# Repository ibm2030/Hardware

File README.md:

# Hardware
Boards for LEDs and switches etc.
Note that the x_PCB pdf is provided for reference only as it excludes the ground and power planes so appears incomplete.

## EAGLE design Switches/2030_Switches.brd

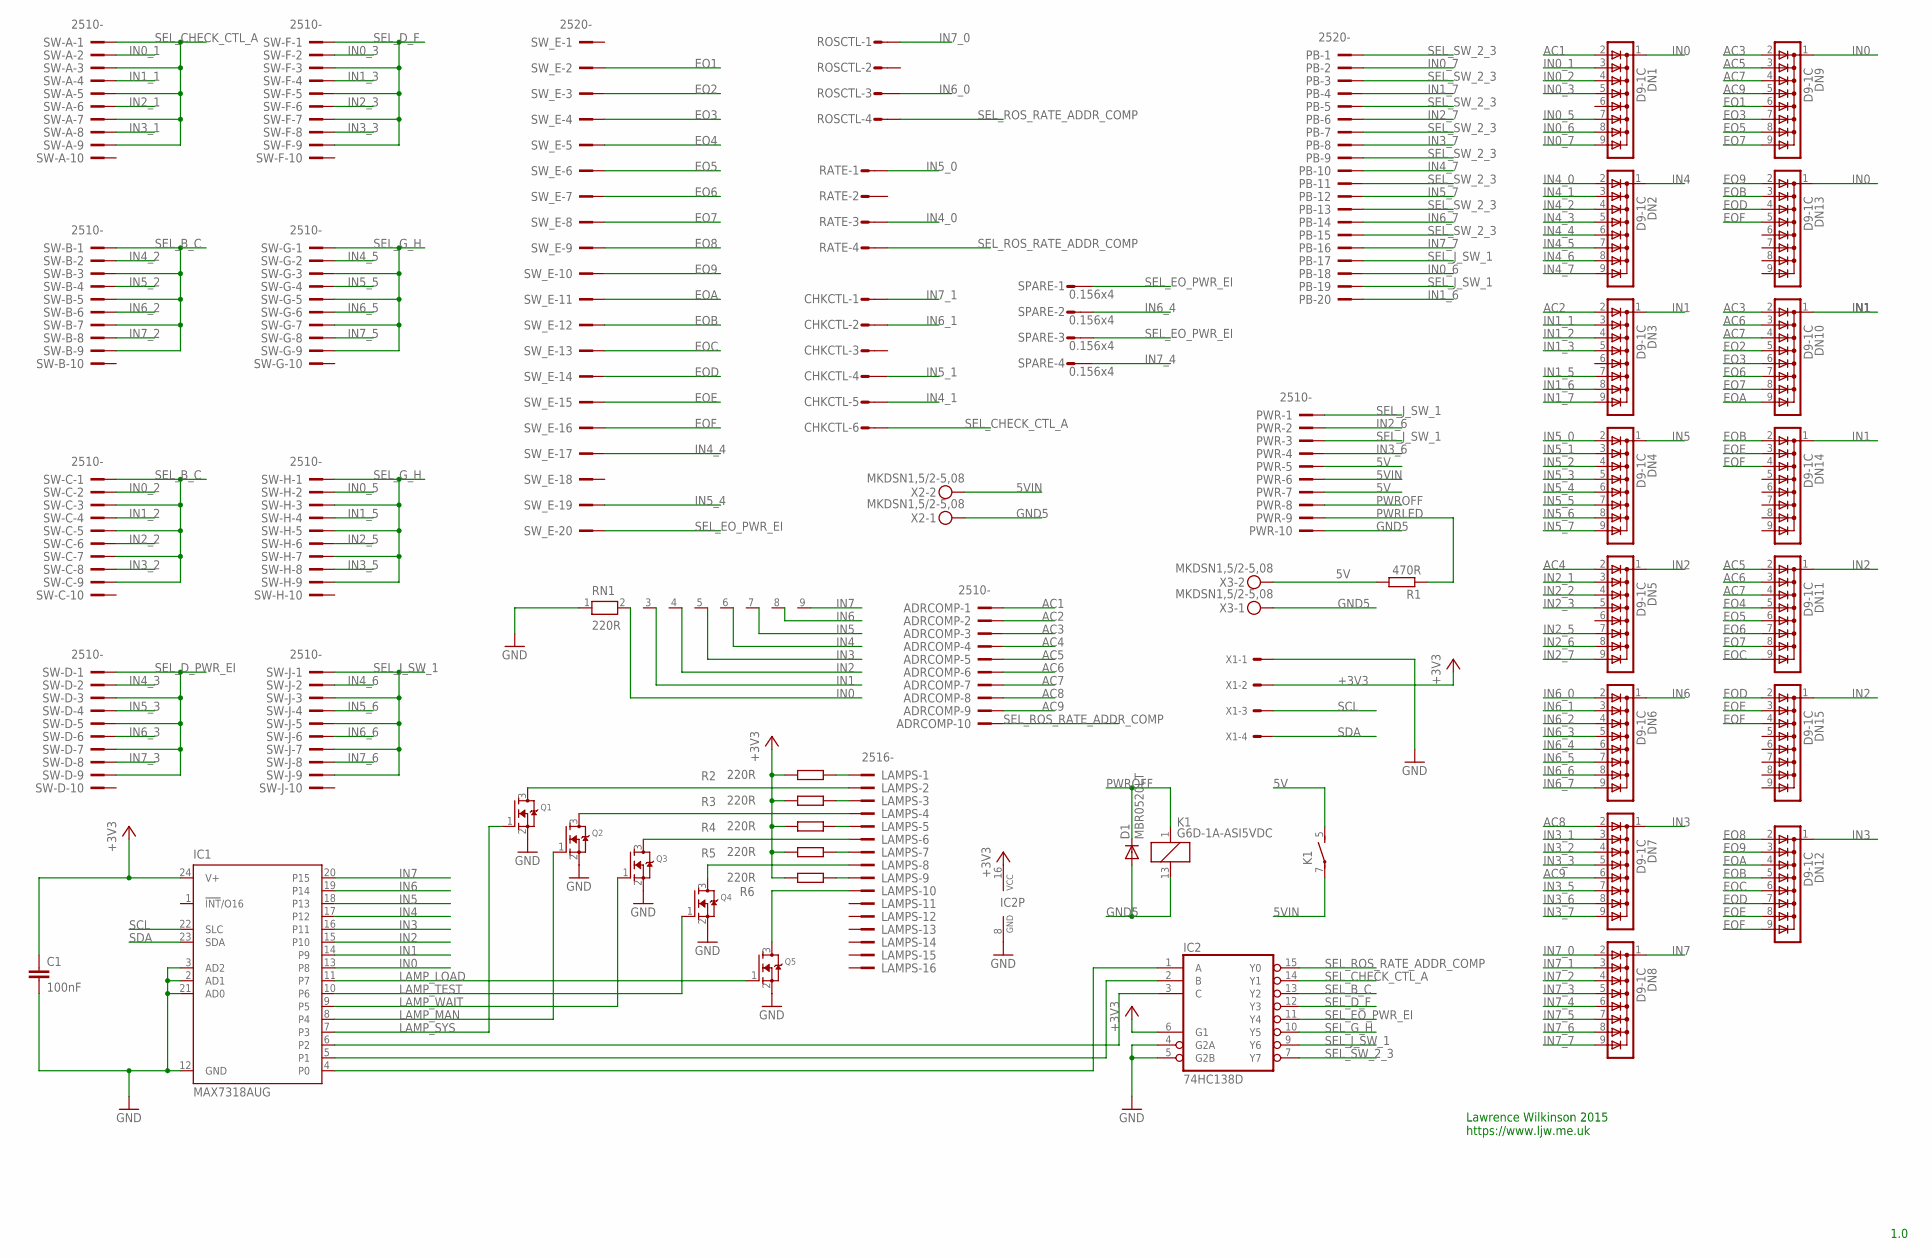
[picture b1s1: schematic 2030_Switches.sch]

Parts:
ADRCOMP: 2510-; PAK100/2500-10
C1: 100nF; C1206
CHKCTL: S06P
D1: MBR0520LT; SOD123
DN1, DN2, DN3, DN4, DN5, DN6, DN7, DN8, DN9, DN10, DN11, DN12, DN13, DN14, DN15: D9-1C; SIL09C
IC1: MAX7318AUG; SO24L
IC2: 74HC138D; SO16
K1: G6D-1A-ASI5VDC; G6D
LAMPS: 2516-; PAK100/2500-16
PB: 2520-; PAK100/2500-20
PWR: 2510-; PAK100/2500-10
Q1, Q2, Q3, Q4, Q5: MOSFET-NREFLOW; SOT23
R1: 470R; M1206
R2, R3, R4, R5, R6: 220R; R0805
RATE: S04P
RN1: 220R; RN-9
ROSCTL: S04P
SPARE: 0.156x4; S04P
SW-A: 2510-; PAK100/2500-10
SW-B: 2510-; PAK100/2500-10
SW-C: 2510-; PAK100/2500-10
SW-D: 2510-; PAK100/2500-10
SW-F: 2510-; PAK100/2500-10
SW-G: 2510-; PAK100/2500-10
SW-H: 2510-; PAK100/2500-10
SW-J: 2510-; PAK100/2500-10
SW_E: 2520-; PAK100/2500-20
X1: KK-156-4
X2, X3: MKDSN1,5/2-5,08

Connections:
5V: K1.5 (S), PWR.5, PWR.7, R1.2, X3.2
5VIN: K1.7, PWR.6, X2.2
+3V3: C1.1, IC1.24 (V+), IC2.6 (G1), IC2.16 (VCC), R2.1, R3.1, R4.1, R5.1, R6.1, X1.2
AC1: ADRCOMP.1, DN1.2
AC2: ADRCOMP.2, DN3.2
AC3: ADRCOMP.3, DN9.2, DN10.2
AC4: ADRCOMP.4, DN5.2
AC5: ADRCOMP.5, DN9.3, DN11.2
AC6: ADRCOMP.6, DN10.3, DN11.3
AC7: ADRCOMP.7, DN9.4, DN10.4, DN11.4
AC8: ADRCOMP.8, DN7.2
AC9: ADRCOMP.9, DN7.6, DN9.5
EO1: DN9.6, SW_E.2
EO2: DN10.5, SW_E.3
EO3: DN9.7, DN10.6, SW_E.4
EO4: DN11.5, SW_E.5
EO5: DN9.8, DN11.6, SW_E.6
EO6: DN10.7, DN11.7, SW_E.7
EO7: DN9.9, DN10.8, DN11.8, SW_E.8
EO8: DN12.2, SW_E.9
EO9: DN12.3, DN13.2, SW_E.10
EOA: DN10.9, DN12.4, SW_E.11
EOB: DN12.5, DN13.3, DN14.2, SW_E.12
EOC: DN11.9, DN12.6, SW_E.13
EOD: DN12.7, DN13.4, DN15.2, SW_E.14
EOE: DN12.8, DN14.3, DN15.3, SW_E.15
EOF: DN12.9, DN13.5, DN14.4, DN15.4, SW_E.16
GND: C1.2, IC1.2 (AD1), IC1.3 (AD2), IC1.12 (GND), IC1.21 (AD0), IC2.4 (G2A), IC2.5 (G2B), IC2.8 (GND), Q1.2 (S), Q2.2 (S), Q3.2 (S), Q4.2 (S), Q5.2 (S), RN1.1, X1.1
GND5: D1.A, K1.13 (2), PWR.10, X2.1, X3.1
IN0: DN1.1 (C), DN9.1 (C), DN13.1 (C), IC1.13 (P8), RN1.2
IN0_1: DN1.3, SW-A.2
IN0_2: DN1.4, SW-C.2
IN0_3: DN1.5, SW-F.2
IN0_5: DN1.7, SW-H.2
IN0_6: DN1.8, PB.18
IN0_7: DN1.9, PB.2
IN1: DN3.1 (C), DN10.1 (C), DN14.1 (C), IC1.14 (P9), RN1.3
IN1_1: DN3.3, SW-A.4
IN1_2: DN3.4, SW-C.4
IN1_3: DN3.5, SW-F.4
IN1_5: DN3.7, SW-H.4
IN1_6: DN3.8, PB.20
IN1_7: DN3.9, PB.4
IN2: DN5.1 (C), DN11.1 (C), DN15.1 (C), IC1.15 (P10), RN1.4
IN2_1: DN5.3, SW-A.6
IN2_2: DN5.4, SW-C.6
IN2_3: DN5.5, SW-F.6
IN2_5: DN5.7, SW-H.6
IN2_6: DN5.8, PWR.2
IN2_7: DN5.9, PB.6
IN3: DN7.1 (C), DN12.1 (C), IC1.16 (P11), RN1.5
IN3_1: DN7.3, SW-A.8
IN3_2: DN7.4, SW-C.8
IN3_3: DN7.5, SW-F.8
IN3_5: DN7.7, SW-H.8
IN3_6: DN7.8, PWR.4
IN3_7: DN7.9, PB.8
IN4: DN2.1 (C), IC1.17 (P12), RN1.6
IN4_0: DN2.2, RATE.3
IN4_1: CHKCTL.5, DN2.3
IN4_2: DN2.4, SW-B.2
IN4_3: DN2.5, SW-D.2
IN4_4: DN2.6, SW_E.17
IN4_5: DN2.7, SW-G.2
IN4_6: DN2.8, SW-J.2
IN4_7: DN2.9, PB.10
IN5: DN4.1 (C), IC1.18 (P13), RN1.7
IN5_0: DN4.2, RATE.1
IN5_1: CHKCTL.4, DN4.3
IN5_2: DN4.4, SW-B.4
IN5_3: DN4.5, SW-D.4
IN5_4: DN4.6, SW_E.19
IN5_5: DN4.7, SW-G.4
IN5_6: DN4.8, SW-J.4
IN5_7: DN4.9, PB.12
IN6: DN6.1 (C), IC1.19 (P14), RN1.8
IN6_0: DN6.2, ROSCTL.3
IN6_1: CHKCTL.2, DN6.3
IN6_2: DN6.4, SW-B.6
IN6_3: DN6.5, SW-D.6
IN6_4: DN6.6, SPARE.2
IN6_5: DN6.7, SW-G.6
IN6_6: DN6.8, SW-J.6
IN6_7: DN6.9, PB.14
IN7: DN8.1 (C), IC1.20 (P15), RN1.9
IN7_0: DN8.2, ROSCTL.1
IN7_1: CHKCTL.1, DN8.3
IN7_2: DN8.4, SW-B.8
IN7_3: DN8.5, SW-D.8
IN7_4: DN8.6, SPARE.4
IN7_5: DN8.7, SW-G.8
IN7_6: DN8.8, SW-J.8
IN7_7: DN8.9, PB.16
LAMP_LOAD: IC1.11 (P7), Q5.1 (G)
LAMP_MAN: IC1.8 (P4), Q2.1 (G)
LAMP_SYS: IC1.7 (P3), Q1.1 (G)
LAMP_TEST: IC1.10 (P6), Q4.1 (G)
LAMP_WAIT: IC1.9 (P5), Q3.1 (G)
unnamed: LAMPS.1, R2.2
unnamed: LAMPS.3, R3.2
unnamed: LAMPS.5, R4.2
unnamed: LAMPS.7, R5.2
unnamed: LAMPS.9, R6.2
unnamed: LAMPS.10, Q5.3 (D)
unnamed: LAMPS.8, Q4.3 (D)
unnamed: LAMPS.6, Q3.3 (D)
unnamed: LAMPS.4, Q2.3 (D)
unnamed: LAMPS.2, Q1.3 (D)
PWRLED: PWR.9, R1.1
PWROFF: D1.C, K1.1, PWR.8
SCAN_0: IC1.4 (P0), IC2.1 (A)
SCAN_1: IC1.5 (P1), IC2.2 (B)
SCAN_2: IC1.6 (P2), IC2.3 (C)
SCL: IC1.22 (SLC), X1.3
SDA: IC1.23 (SDA), X1.4
SEL_B_C: IC2.13 (Y2), SW-B.1, SW-B.3, SW-B.5, SW-B.7, SW-B.9, SW-C.1, SW-C.3, SW-C.5, SW-C.7, SW-C.9
SEL_CHECK_CTL_A: CHKCTL.6, IC2.14 (Y1), SW-A.1, SW-A.3, SW-A.5, SW-A.7, SW-A.9
SEL_D_F: IC2.12 (Y3), SW-F.1, SW-F.3, SW-F.5, SW-F.7, SW-F.9
SEL_D_PWR_EI: SW-D.1, SW-D.3, SW-D.5, SW-D.7, SW-D.9
SEL_EO_PWR_EI: IC2.11 (Y4), SPARE.1, SPARE.3, SW_E.20
SEL_G_H: IC2.10 (Y5), SW-G.1, SW-G.3, SW-G.5, SW-G.7, SW-G.9, SW-H.1, SW-H.3, SW-H.5, SW-H.7, SW-H.9
SEL_J_SW_1: IC2.9 (Y6), PB.17, PB.19, PWR.1, PWR.3, SW-J.1, SW-J.3, SW-J.5, SW-J.7, SW-J.9
SEL_ROS_RATE_ADDR_COMP: ADRCOMP.10, IC2.15 (Y0), RATE.4, ROSCTL.4
SEL_SW_2_3: IC2.7 (Y7), PB.1, PB.3, PB.5, PB.7, PB.9, PB.11, PB.13, PB.15

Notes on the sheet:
1.0
Lawrence Wilkinson 2015 https://www.ljw.me.uk

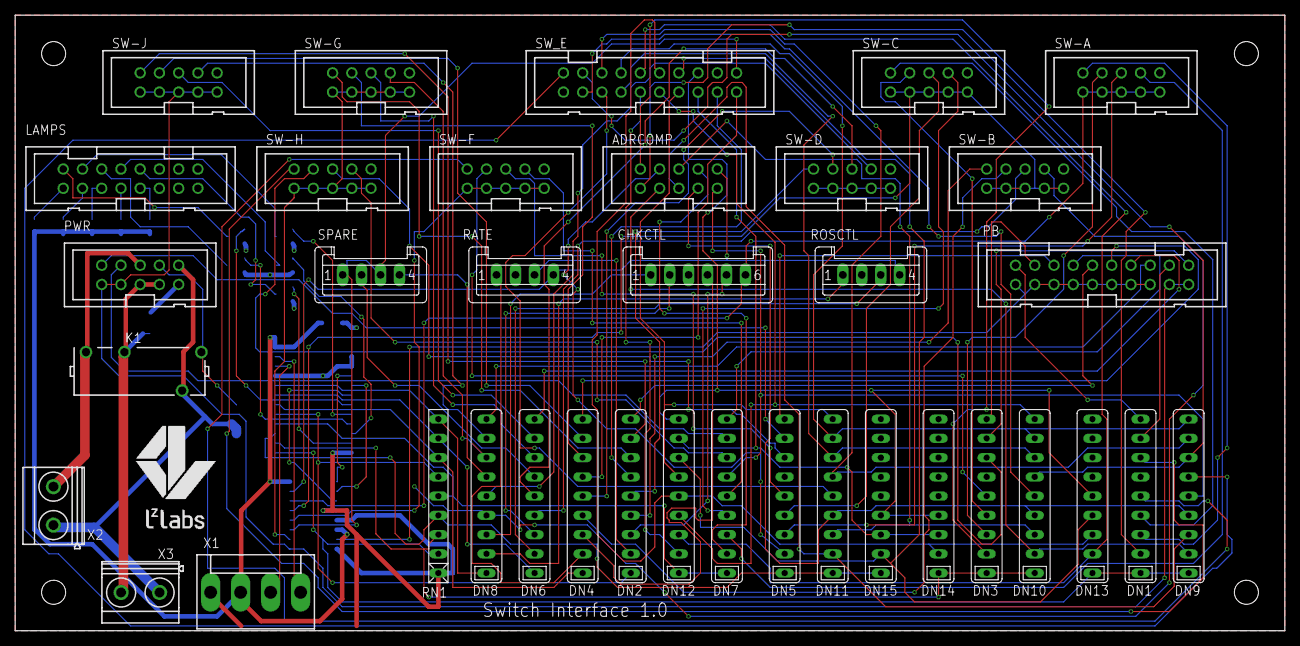
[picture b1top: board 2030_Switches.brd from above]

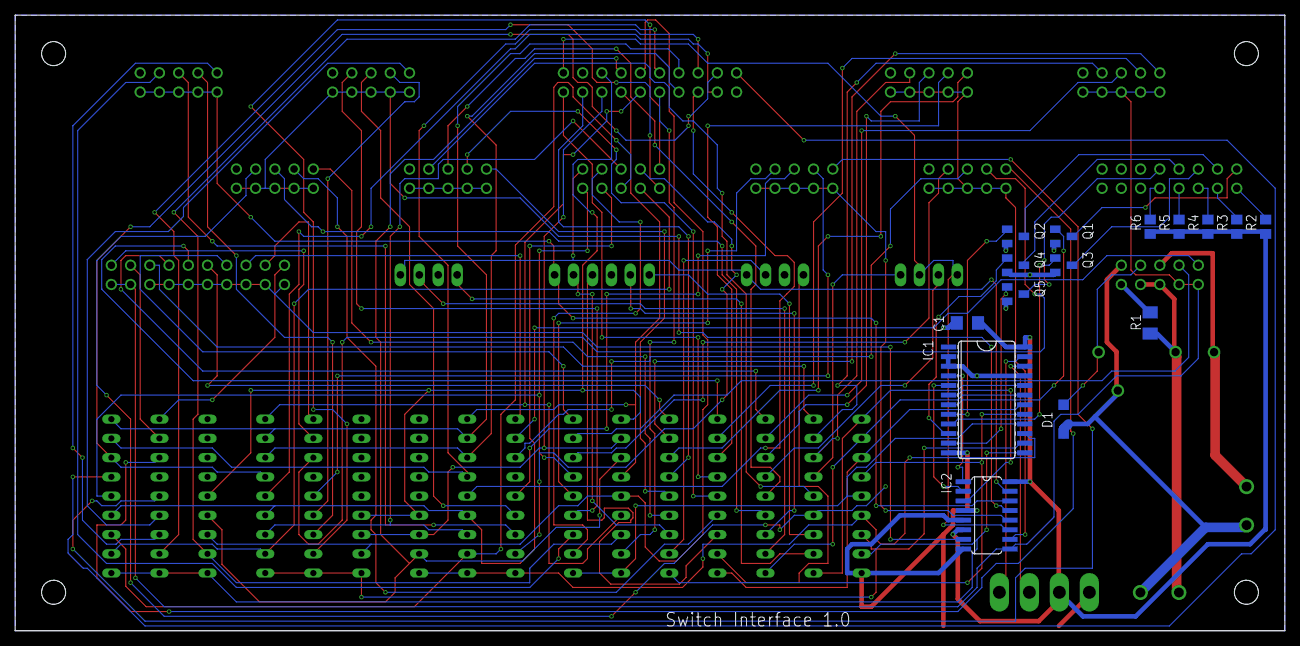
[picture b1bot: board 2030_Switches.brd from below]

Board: 2 copper layers, 167.6 x 81.3 mm, 52 parts (15 on the bottom side), 124 nets.

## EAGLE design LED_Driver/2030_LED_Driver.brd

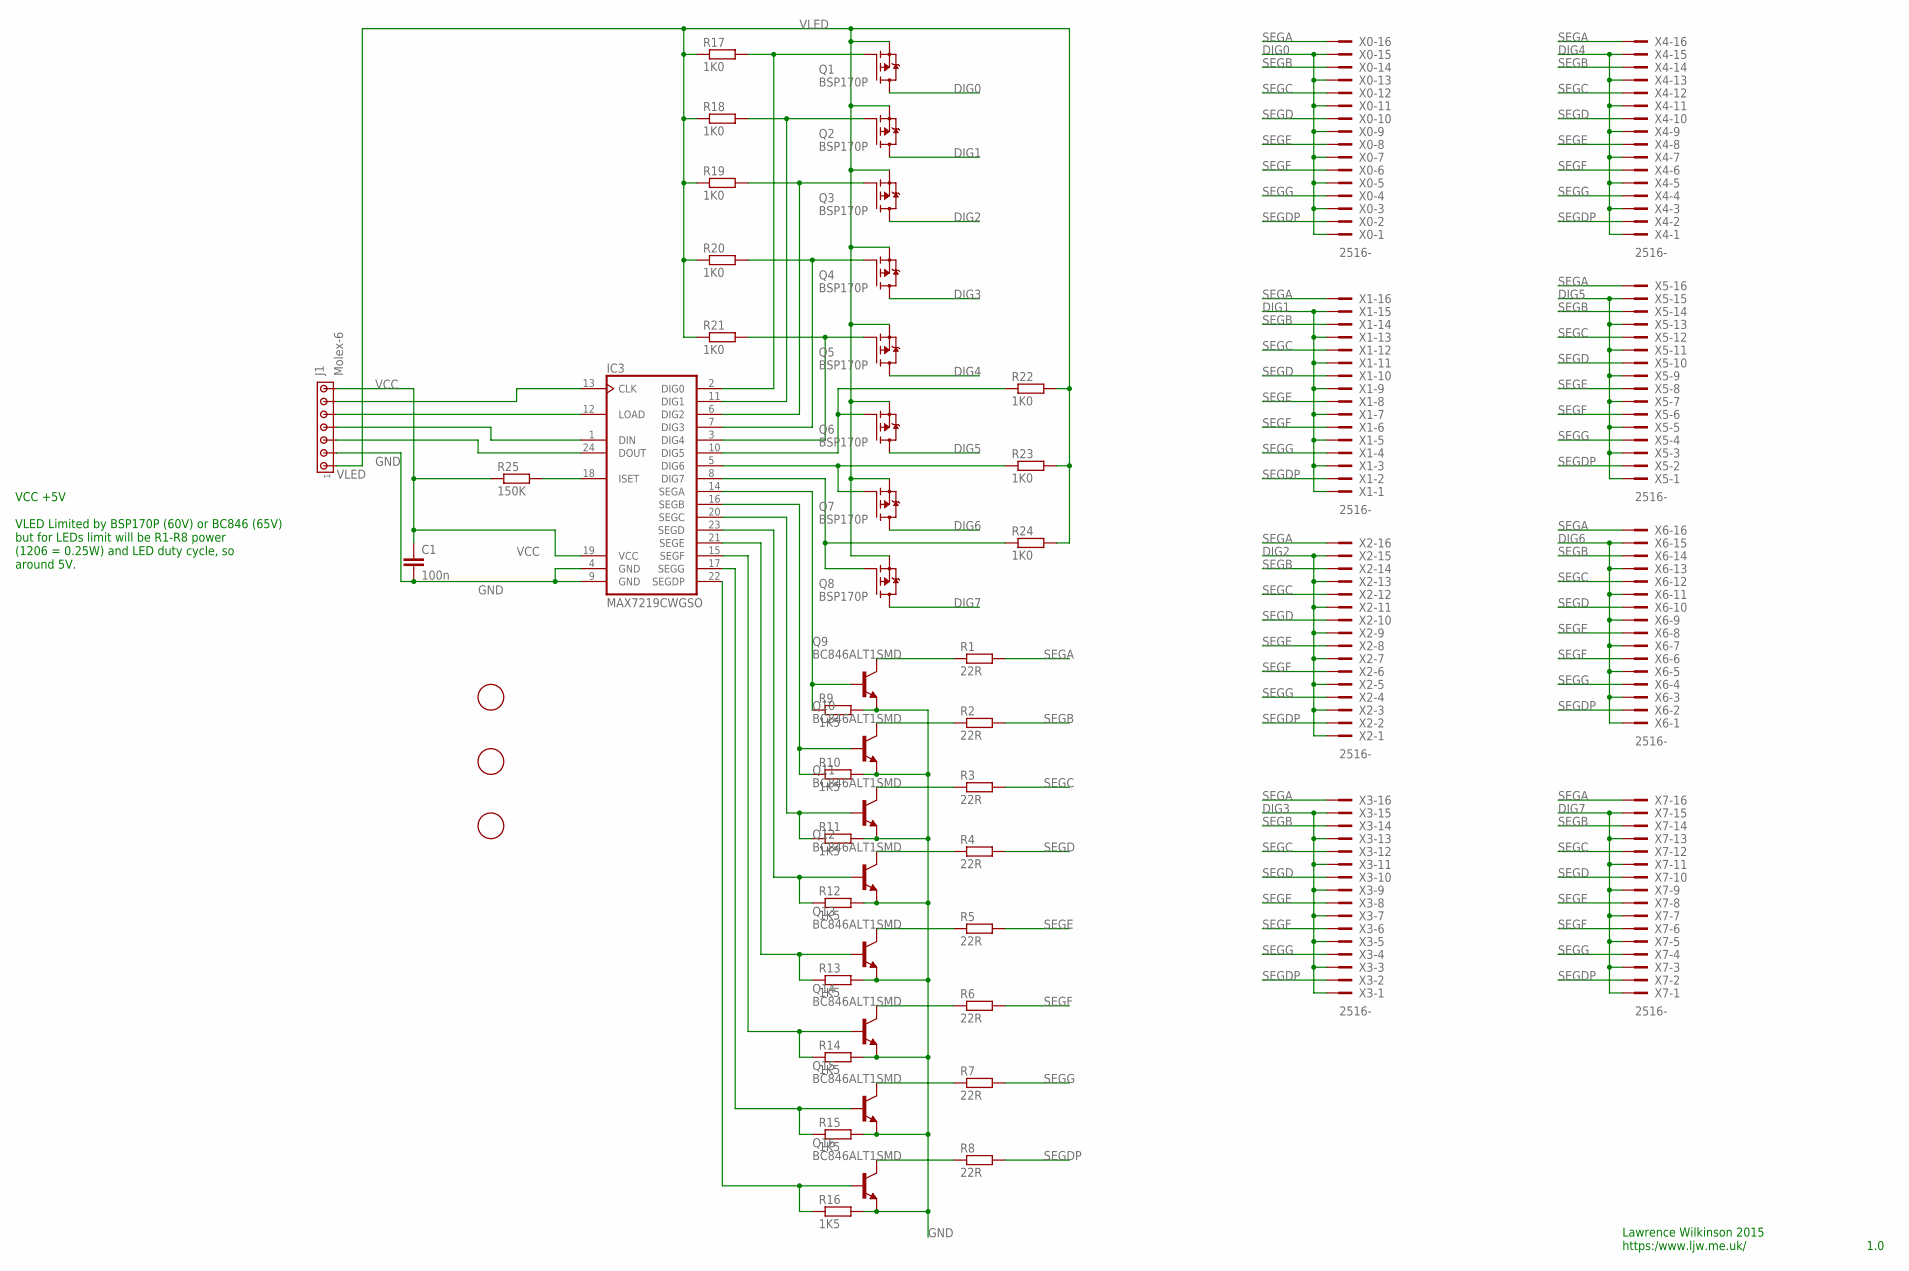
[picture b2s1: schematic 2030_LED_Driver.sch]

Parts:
C1: 100n; C1206
IC3: MAX7219CWGSO; SO24L
J1: Molex-6; 10X07MTA
Q1, Q2, Q3, Q4, Q5, Q6, Q7, Q8: BSP170P; SOT223
Q9, Q10, Q11, Q12, Q13, Q14, Q15, Q16: BC846ALT1SMD; SOT23
R1, R2, R3, R4, R5, R6, R7, R8: 22R; M1206
R9, R10, R11, R12, R13, R14, R15, R16: 1K5; M0805
R17, R18, R19, R20, R21, R22, R23, R24: 1K0; M0805
R25: 150K; M0805
U$1, U$2, U$3: FIDUCIAL; FIDUCIAL_1MM
X0, X1, X2, X3, X4, X5, X6, X7: 2516-; PAK100/2500-16

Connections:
CLK: IC3.13 (CLK), J1.6
DIG0: Q1.2 (D), Q1.4 (D), X0.1, X0.3, X0.5, X0.7, X0.9, X0.11, X0.13, X0.15
DIG1: Q2.2 (D), Q2.4 (D), X1.1, X1.3, X1.5, X1.7, X1.9, X1.11, X1.13, X1.15
DIG2: Q3.2 (D), Q3.4 (D), X2.1, X2.3, X2.5, X2.7, X2.9, X2.11, X2.13, X2.15
DIG3: Q4.2 (D), Q4.4 (D), X3.1, X3.3, X3.5, X3.7, X3.9, X3.11, X3.13, X3.15
DIG4: Q5.2 (D), Q5.4 (D), X4.1, X4.3, X4.5, X4.7, X4.9, X4.11, X4.13, X4.15
DIG5: Q6.2 (D), Q6.4 (D), X5.1, X5.3, X5.5, X5.7, X5.9, X5.11, X5.13, X5.15
DIG6: Q7.2 (D), Q7.4 (D), X6.1, X6.3, X6.5, X6.7, X6.9, X6.11, X6.13, X6.15
DIG7: Q8.2 (D), Q8.4 (D), X7.1, X7.3, X7.5, X7.7, X7.9, X7.11, X7.13, X7.15
DIN: IC3.1 (DIN), J1.4
DOUT: IC3.24 (DOUT), J1.3
GND: C1.2, IC3.4 (GND), IC3.9 (GND), J1.2, Q9.2 (E), Q10.2 (E), Q11.2 (E), Q12.2 (E), Q13.2 (E), Q14.2 (E), Q15.2 (E), Q16.2 (E), R9.2, R10.2, R11.2, R12.2, R13.2, R14.2, R15.2, R16.2
LOAD: IC3.12 (LOAD), J1.5
unnamed: IC3.2 (DIG0), Q1.1 (G), R17.2
unnamed: IC3.11 (DIG1), Q2.1 (G), R18.2
unnamed: IC3.6 (DIG2), Q3.1 (G), R19.2
unnamed: IC3.7 (DIG3), Q4.1 (G), R20.2
unnamed: IC3.3 (DIG4), Q5.1 (G), R21.2
unnamed: IC3.10 (DIG5), Q6.1 (G), R22.1
unnamed: IC3.5 (DIG6), Q7.1 (G), R23.1
unnamed: IC3.8 (DIG7), Q8.1 (G), R24.1
unnamed: IC3.18 (ISET), R25.2
unnamed: Q9.3 (C), R1.1
unnamed: Q10.3 (C), R2.1
unnamed: Q11.3 (C), R3.1
unnamed: Q12.3 (C), R4.1
unnamed: Q13.3 (C), R5.1
unnamed: IC3.14 (SEGA), Q9.1 (B), R9.1
unnamed: IC3.16 (SEGB), Q10.1 (B), R10.1
unnamed: IC3.20 (SEGC), Q11.1 (B), R11.1
unnamed: IC3.23 (SEGD), Q12.1 (B), R12.1
unnamed: IC3.21 (SEGE), Q13.1 (B), R13.1
unnamed: IC3.15 (SEGF), Q14.1 (B), R14.1
unnamed: IC3.17 (SEGG), Q15.1 (B), R15.1
unnamed: IC3.22 (SEGDP), Q16.1 (B), R16.1
unnamed: Q14.3 (C), R6.1
unnamed: Q15.3 (C), R7.1
unnamed: Q16.3 (C), R8.1
SEGA: R1.2, X0.16, X1.16, X2.16, X3.16, X4.16, X5.16, X6.16, X7.16
SEGB: R2.2, X0.14, X1.14, X2.14, X3.14, X4.14, X5.14, X6.14, X7.14
SEGC: R3.2, X0.12, X1.12, X2.12, X3.12, X4.12, X5.12, X6.12, X7.12
SEGD: R4.2, X0.10, X1.10, X2.10, X3.10, X4.10, X5.10, X6.10, X7.10
SEGDP: R8.2, X0.2, X1.2, X2.2, X3.2, X4.2, X5.2, X6.2, X7.2
SEGE: R5.2, X0.8, X1.8, X2.8, X3.8, X4.8, X5.8, X6.8, X7.8
SEGF: R6.2, X0.6, X1.6, X2.6, X3.6, X4.6, X5.6, X6.6, X7.6
SEGG: R7.2, X0.4, X1.4, X2.4, X3.4, X4.4, X5.4, X6.4, X7.4
VCC: C1.1, IC3.19 (VCC), J1.7, R25.1
VLED: J1.1, Q1.3 (S), Q2.3 (S), Q3.3 (S), Q4.3 (S), Q5.3 (S), Q6.3 (S), Q7.3 (S), Q8.3 (S), R17.1, R18.1, R19.1, R20.1, R21.1, R22.2, R23.2, R24.2

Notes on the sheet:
1.0
VCC +5V VLED Limited by BSP170P (60V) or BC846 (65V) but for LEDs limit will be R1-R8 power (1206 = 0.25W) and LED duty cycle, so around 5V.
Lawrence Wilkinson 2015 https:/www.ljw.me.uk/

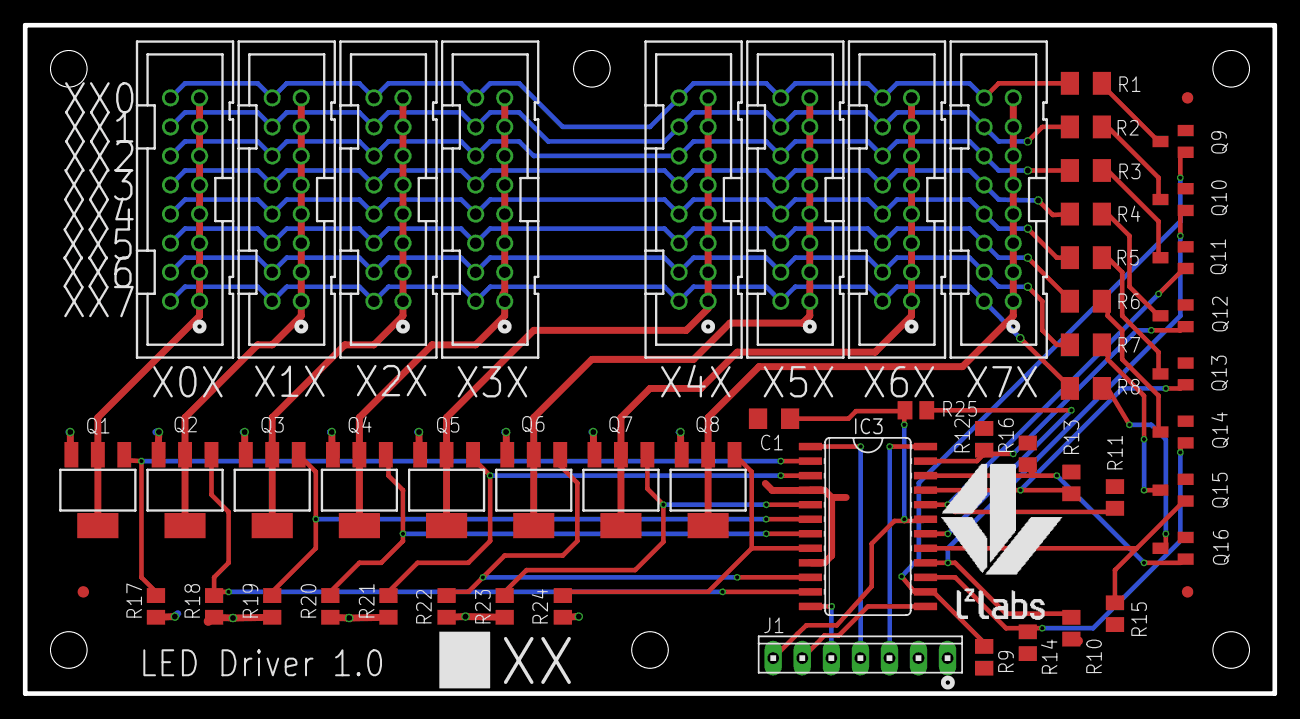
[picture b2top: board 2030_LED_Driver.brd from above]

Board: 2 copper layers, 109.2 x 58.4 mm, 55 parts (0 on the bottom side), 48 nets.

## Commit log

2025-11-10 Initial version v1.0
2025-11-10 Add PCB top/bottom
2025-11-11 Add note about x_PCB pdf reference
    Clarify the purpose of the x_PCB pdf in the README.
